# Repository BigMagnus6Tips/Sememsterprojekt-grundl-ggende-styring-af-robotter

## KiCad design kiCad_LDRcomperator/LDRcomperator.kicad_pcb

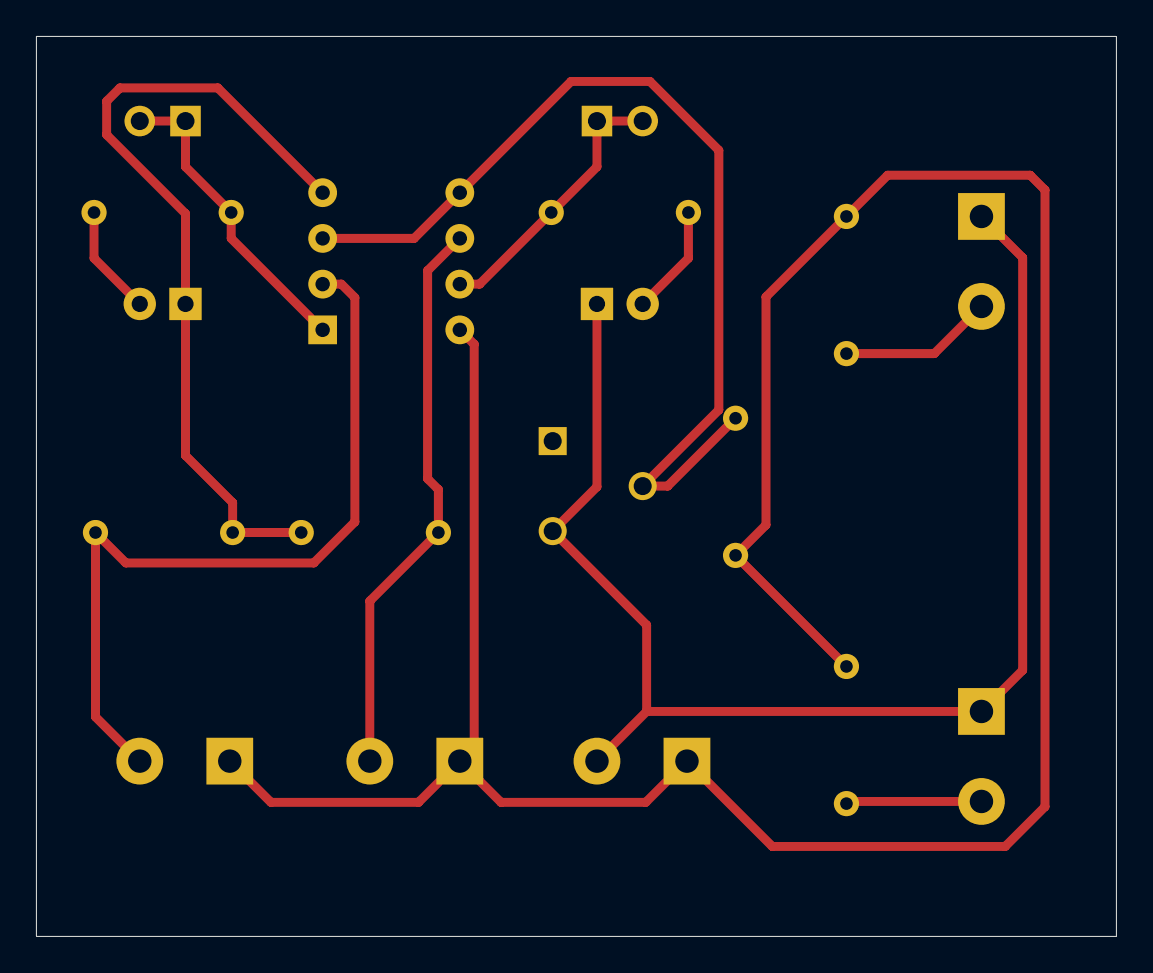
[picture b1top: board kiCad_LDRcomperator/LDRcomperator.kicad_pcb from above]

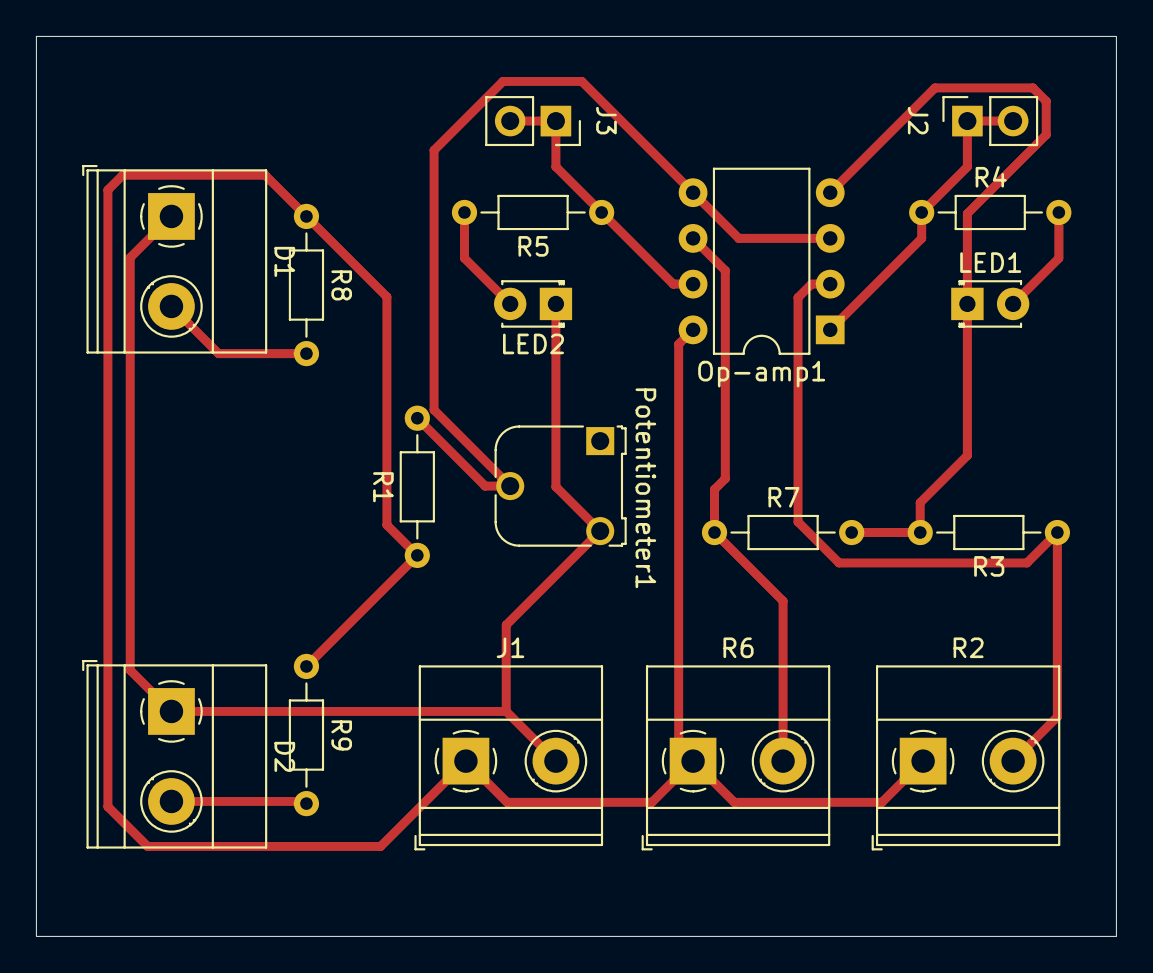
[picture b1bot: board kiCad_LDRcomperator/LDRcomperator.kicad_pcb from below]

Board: 2 copper layers, 60.0 x 50.0 mm, 18 parts (18 on the bottom side), 11 nets.

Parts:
D1, D2: LED; TerminalBlock_Phoenix_MKDS-1,5-2_1x02_P5.00mm_Horizontal
J1: Screw_Terminal_01x02; TerminalBlock_Phoenix_MKDS-1,5-2_1x02_P5.00mm_Horizontal
J2, J3: Conn_01x02_MountingPin; PinSocket_1x02_P2.54mm_Vertical
LED1, LED2: LED; LED_D1.8mm_W3.3mm_H2.4mm
Op-amp1: MCP6001R; DIP-8_W7.62mm
Potentiometer1: 100k ohm; Potentiometer_Runtron_RM-065_Vertical
R1: 22k ohm; R_Axial_DIN0204_L3.6mm_D1.6mm_P7.62mm_Horizontal
R2, R6: LDR03; TerminalBlock_Phoenix_MKDS-1,5-2_1x02_P5.00mm_Horizontal
R3: 2k ohm; R_Axial_DIN0204_L3.6mm_D1.6mm_P7.62mm_Horizontal
R4, R5: 65 ohm; R_Axial_DIN0204_L3.6mm_D1.6mm_P7.62mm_Horizontal
R7: 2,2k ohm; R_Axial_DIN0204_L3.6mm_D1.6mm_P7.62mm_Horizontal
R8, R9: 30; R_Axial_DIN0204_L3.6mm_D1.6mm_P7.62mm_Horizontal

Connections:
+3V3: J1.1, Op-amp1.8 (V+), R1.1, R2.1, R6.1, R8.1, R9.1
GND: D1.1 (K), D2.1 (K), J1.2, LED1.1 (K), LED2.1 (K), Op-amp1.4 (V-), Potentiometer1.3, R3.2, R7.2
unnamed: D1.2 (A), R8.2
unnamed: D2.2 (A), R9.2
unnamed: J2.1, J2.2, Op-amp1.1, R4.1
unnamed: J3.1, J3.2, Op-amp1.7, R5.1
unnamed: LED1.2 (A), R4.2
unnamed: LED2.2 (A), R5.2
unnamed: Op-amp1.3 (+), Op-amp1.5 (+), Potentiometer1.2, R1.2
unnamed: Op-amp1.2 (-), R2.2, R3.1
unnamed: Op-amp1.6 (-), R6.2, R7.1

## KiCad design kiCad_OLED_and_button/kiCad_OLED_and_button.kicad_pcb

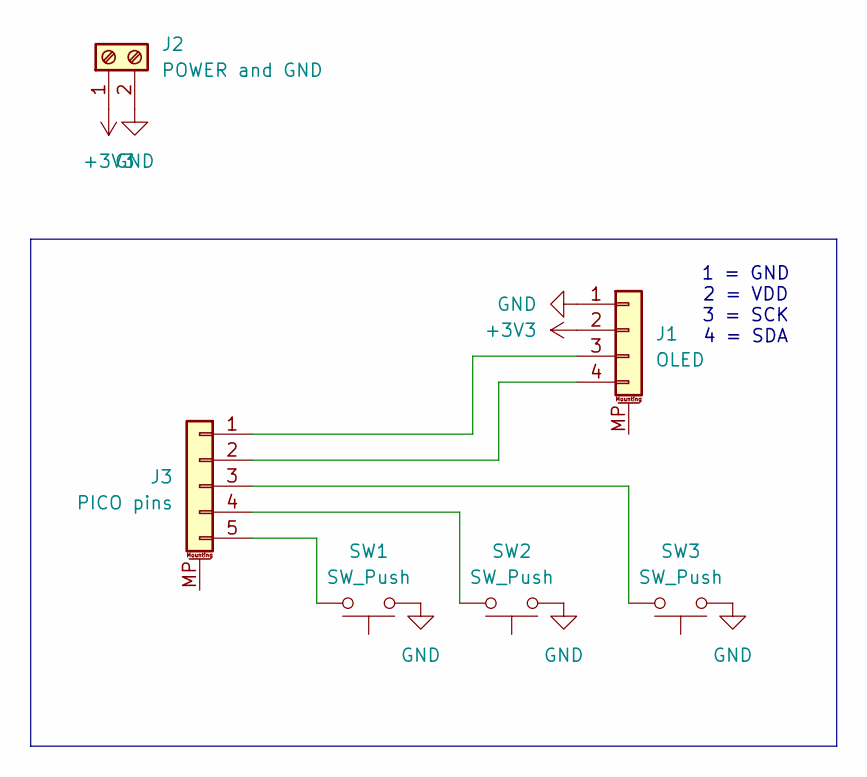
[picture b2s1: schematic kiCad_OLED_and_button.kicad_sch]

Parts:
J1: OLED; PinSocket_1x04_P2.54mm_Vertical
J2: POWER and GND; TerminalBlock_Phoenix_MKDS-1,5-2_1x02_P5.00mm_Horizontal
J3: PICO pins; PinSocket_1x05_P2.54mm_Vertical
SW1, SW2, SW3: SW_Push; SW_PUSH_6mm_H4.3mm

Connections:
+3V3: J1.2 (VDD), J2.1
GND: J1.1 (GND), J2.2, SW1.1, SW2.1, SW3.1
unnamed: J1.3 (SCK), J3.1
unnamed: J1.4 (SDA), J3.2
unnamed: J3.3, SW3.2
unnamed: J3.4, SW2.2
unnamed: J3.5, SW1.2

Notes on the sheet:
1 = GND 2 = VDD 3 = SCK 4 = SDA

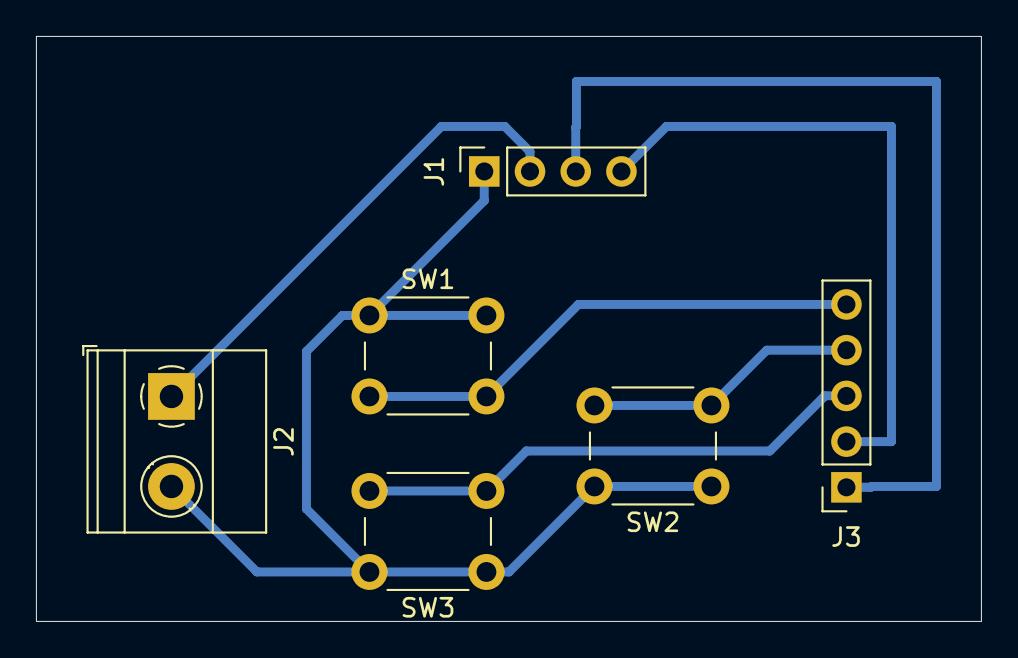
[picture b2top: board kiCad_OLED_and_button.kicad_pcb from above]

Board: 2 copper layers, 52.5 x 32.5 mm, 6 parts (0 on the bottom side), 7 nets.

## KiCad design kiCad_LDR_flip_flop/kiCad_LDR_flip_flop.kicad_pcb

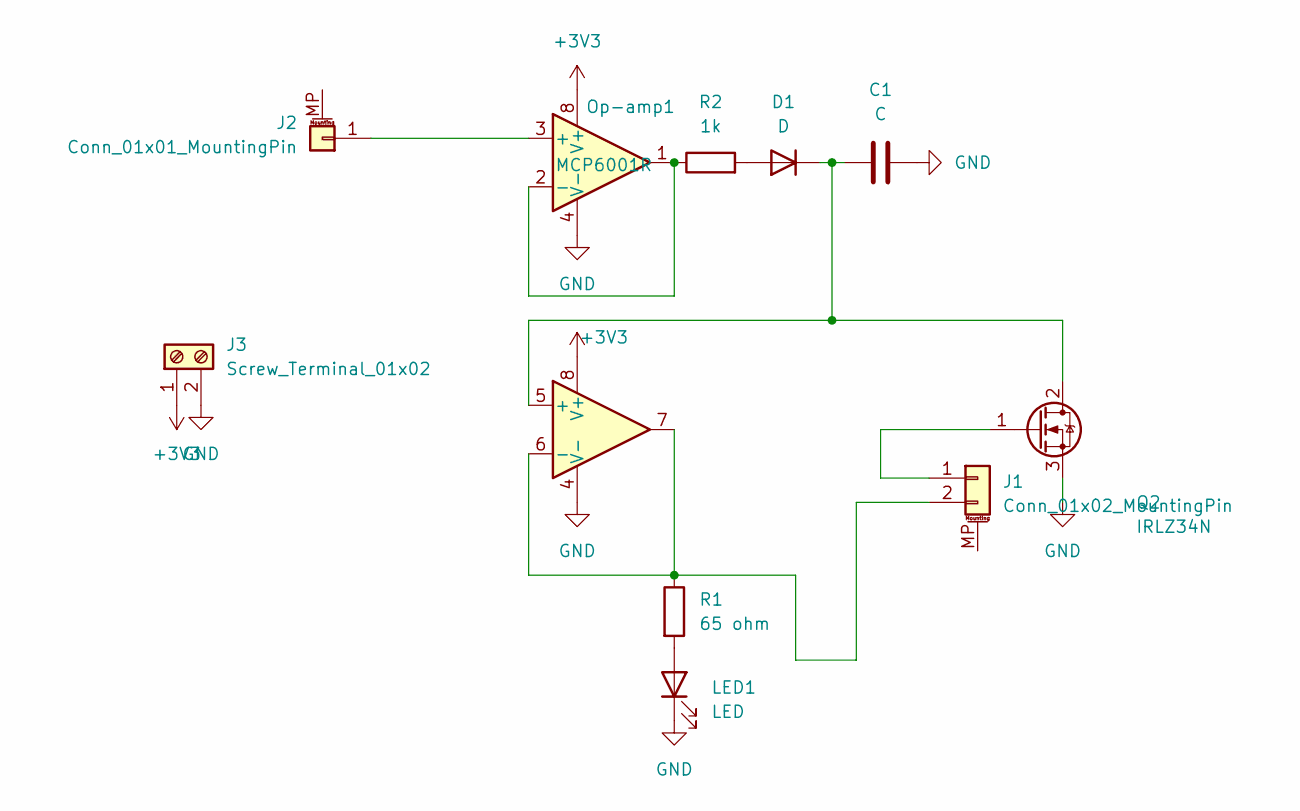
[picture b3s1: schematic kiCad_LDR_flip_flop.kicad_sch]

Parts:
C1: C; C_Disc_D11.0mm_W5.0mm_P5.00mm
D1: D; D_5W_P10.16mm_Horizontal
J1: Conn_01x02_MountingPin; PinSocket_1x02_P2.54mm_Vertical
J2: Conn_01x01_MountingPin; PinSocket_1x01_P2.54mm_Vertical
J3: Screw_Terminal_01x02; TerminalBlock_Phoenix_MKDS-1,5-2_1x02_P5.00mm_Horizontal
LED1: LED; LED_D1.8mm_W3.3mm_H2.4mm
Op-amp1: MCP6001R; DIP-8_W7.62mm
Q2: IRLZ34N; TO-220-3_Vertical
R1: 65 ohm; R_Axial_DIN0204_L3.6mm_D1.6mm_P7.62mm_Horizontal
R2: 1k; R_Axial_DIN0204_L3.6mm_D1.6mm_P7.62mm_Horizontal

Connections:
+3V3: J3.1, Op-amp1.8 (V+)
GND: C1.2, J3.2, LED1.1 (K), Op-amp1.4 (V-), Q2.3 (S)
unnamed: D1.2 (A), R2.2
unnamed: C1.1, D1.1 (K), Op-amp1.5 (+), Q2.2 (D)
unnamed: J1.1, Q2.1 (G)
unnamed: J1.2, Op-amp1.6 (-), Op-amp1.7, R1.1
unnamed: J2.1, Op-amp1.3 (+)
unnamed: LED1.2 (A), R1.2
unnamed: Op-amp1.1, Op-amp1.2 (-), R2.1

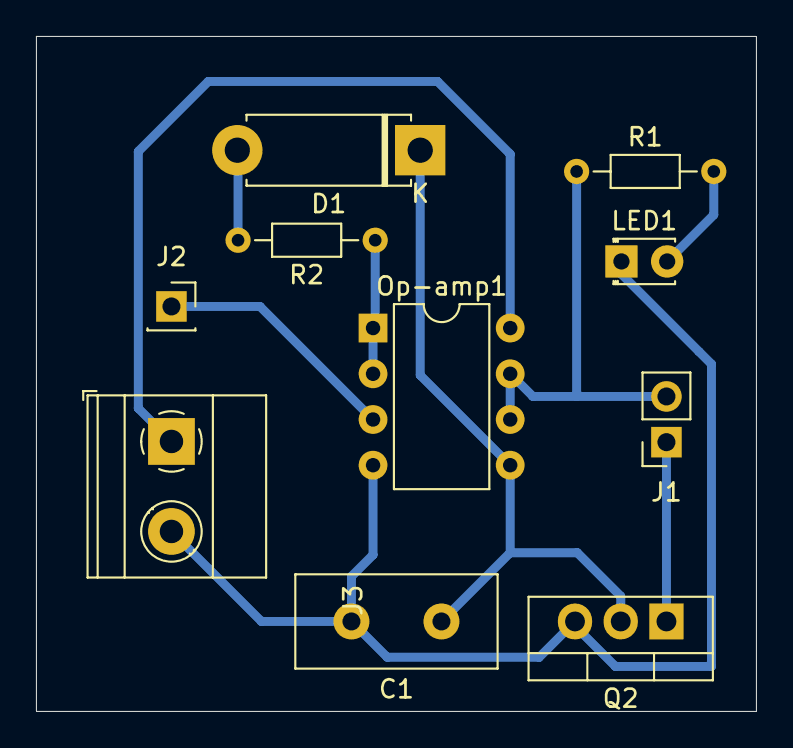
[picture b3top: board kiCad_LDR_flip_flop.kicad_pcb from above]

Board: 2 copper layers, 40.0 x 37.5 mm, 10 parts (0 on the bottom side), 9 nets.

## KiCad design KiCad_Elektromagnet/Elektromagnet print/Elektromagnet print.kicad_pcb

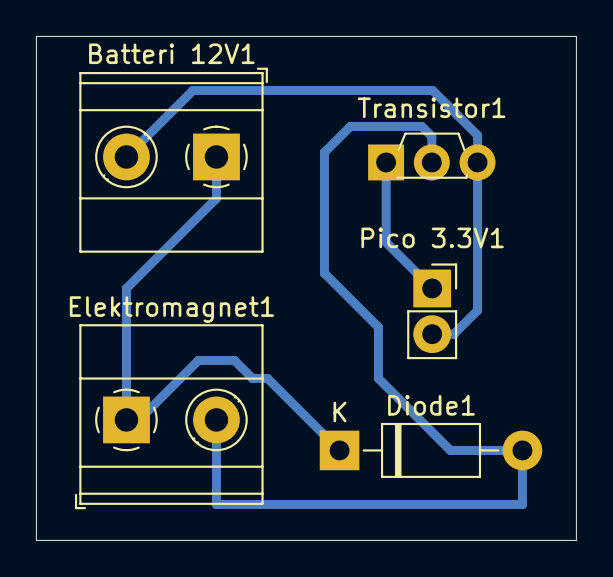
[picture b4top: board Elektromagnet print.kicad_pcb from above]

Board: 2 copper layers, 30.0 x 28.0 mm, 5 parts (0 on the bottom side), 4 nets.

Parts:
Batteri 12V1: Screw_Terminal_01x02; TerminalBlock_Phoenix_MKDS-1,5-2_1x02_P5.00mm_Horizontal
Diode1: 1N4001; D_DO-41_SOD81_P10.16mm_Horizontal
Elektromagnet1: L; TerminalBlock_Phoenix_MKDS-1,5-2_1x02_P5.00mm_Horizontal
Pico 3.3V1: Conn_01x01_Pin; PinSocket_1x02_P2.54mm_Vertical
Transistor1: 2N7000; TO-92S_Wide

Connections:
GND: Batteri 12V1.2, Pico 3.3V1.2 (Pin_1), Transistor1.3 (D)
unnamed: Batteri 12V1.1, Diode1.1 (K), Elektromagnet1.1
unnamed: Diode1.2 (A), Elektromagnet1.2, Transistor1.2 (G)
unnamed: Pico 3.3V1.1, Transistor1.1 (S)

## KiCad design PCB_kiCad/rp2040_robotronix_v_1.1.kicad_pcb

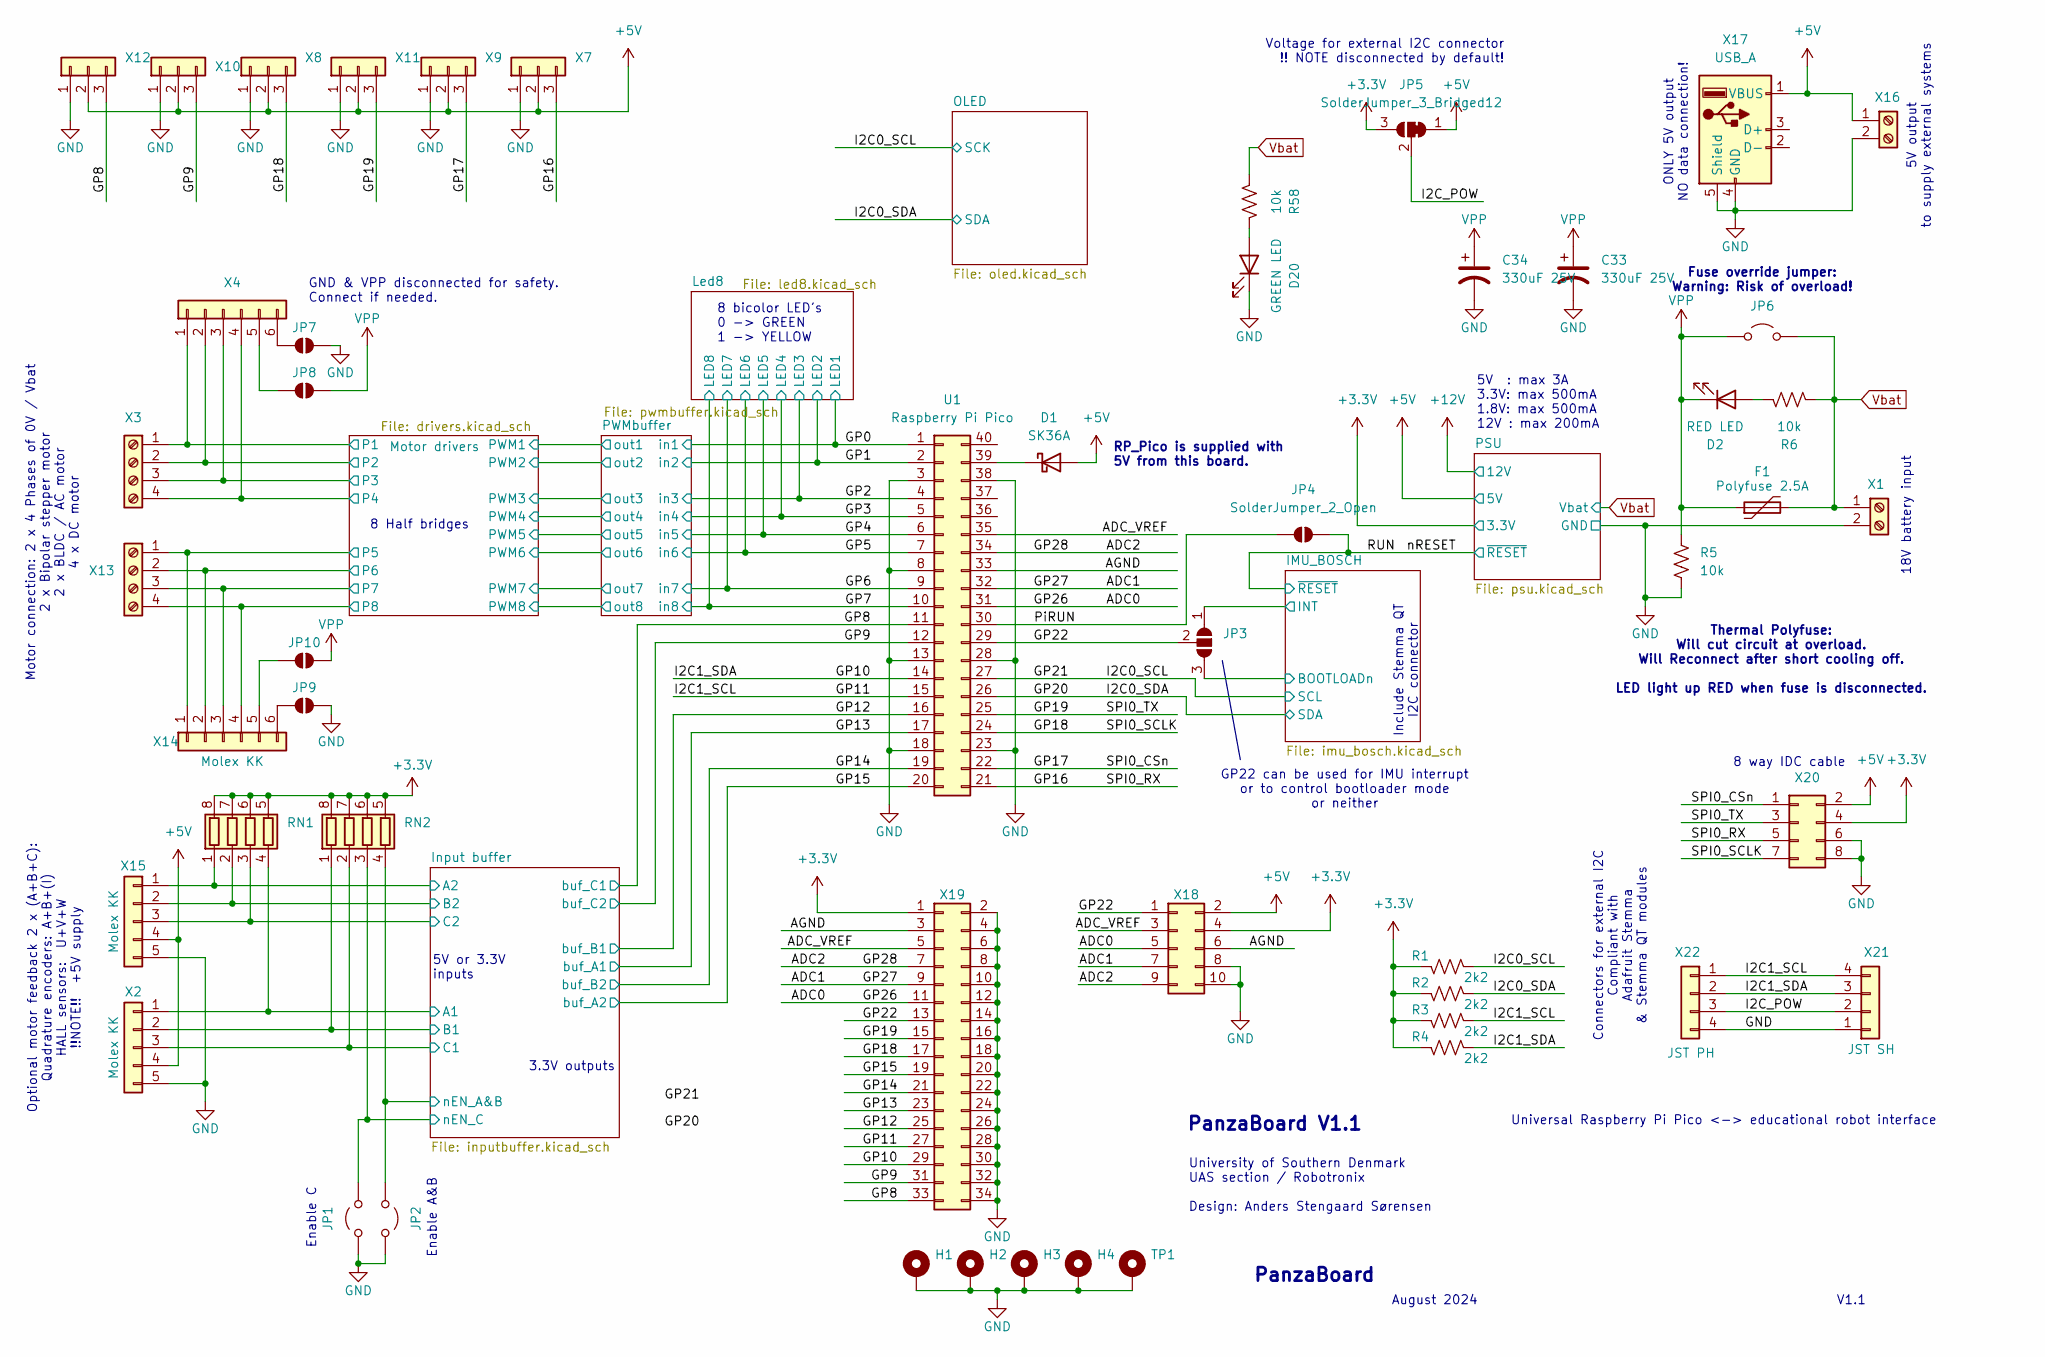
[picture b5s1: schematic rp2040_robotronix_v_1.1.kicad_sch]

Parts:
C33, C34: 330uF 25V; CP_Radial_D10.0mm_P5.00mm; MFR# Wurth Elektronik
D1: SK36A; D_SMA; MFR# Micro Commercial Components (MCC)
D2: RED LED; LED_0603_1608Metric; MFR# Wurth Elektronik
D20: GREEN LED; LED_0603_1608Metric; MFR# Wurth Elektronik
F1: Polyfuse 2.5A; Fuse_2920_7451Metric; MFR# Littlefuse
H1, H2, H3, H4: MountingHole_Pad; MountingHole_3.2mm_M3_Pad
JP1, JP2, JP6: Jumper_2_Open; SolderJumper-2_P1.3mm_Open_TrianglePad1.0x1.5mm
JP3: SolderJumper_3_Open; PinHeader_1x03_P2.54mm_Vertical
JP4, JP7, JP8, JP9, JP10: SolderJumper_2_Open; SolderJumper-2_P1.3mm_Open_Pad1.0x1.5mm
JP5: SolderJumper_3_Bridged12; SolderJumper-3_P1.3mm_Bridged12_Pad1.0x1.5mm_NumberLabels
R1, R2, R3, R4: 2k2; R_0603_1608Metric
R5, R6, R58: 10k; R_0603_1608Metric
RN1, RN2: 10k; R_Array_Convex_4x0402
TP1: MountingHole_Pad; MountingHole_3.2mm_M3_Pad
U1: Raspberry Pi Pico; RP_pico
X1: Screw_Terminal_01x02; TerminalBlock_Phoenix_PT-1,5-2-5.0-H_1x02_P5.00mm_Horizontal; MFR# Amphenol Anytek
X2, X15: Molex KK; Molex_KK-254_AE-6410-05A_1x05_P2.54mm_Vertical
X3, X13: Screw_Terminal_01x04; TerminalBlock_Phoenix_PT-1,5-4-3.5-H_1x04_P3.50mm_Horizontal; MFR# Phoenix Contact
X4: Conn_01x06; Molex_KK-254_AE-6410-06A_1x06_P2.54mm_Vertical
X7, X8, X9, X10, X11, X12: Conn_01x03; PinHeader_1x03_P2.54mm_Vertical
X14: Molex KK; Molex_KK-254_AE-6410-06A_1x06_P2.54mm_Vertical
X16: Screw_Terminal_01x02; TerminalBlock_Phoenix_PT-1,5-2-3.5-H_1x02_P3.50mm_Horizontal
X17: USB_A; USB_A_Molex_67643_Horizontal
X18: Conn_02x05_Odd_Even; IDC-Header_2x05_P2.54mm_Vertical
X19: Conn_02x17_Odd_Even; IDC-Header_2x17_P2.54mm_Vertical
X20: Conn_02x04_Odd_Even; PinHeader_2x04_P2.54mm_Vertical
X21: JST SH; JST_SH_SM04B-SRSS-TB_1x04-1MP_P1.00mm_Horizontal
X22: JST PH; JST_PH_S4B-PH-K_1x04_P2.00mm_Horizontal

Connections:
+5V: D1.2 (A), JP5.1 (A), X2.4, X7.2, X8.2, X9.2, X10.2, X11.2, X12.2, X15.4, X16.1, X17.1 (VBUS), X18.2, X20.2; also elsewhere on the board
/ADC0: U1.31, X18.5, X19.11
/ADC1: U1.32, X18.7, X19.9
/ADC2: U1.34, X18.9, X19.7
/ADC_VREF: U1.35, X18.3, X19.5
/AGND: U1.33, X18.6, X19.3
/GP0: U1.1; also elsewhere on the board
/GP1: U1.2; also elsewhere on the board
/GP2: U1.4; also elsewhere on the board
/GP3: U1.5; also elsewhere on the board
/GP4: U1.6; also elsewhere on the board
/GP5: U1.7; also elsewhere on the board
/GP6: U1.9; also elsewhere on the board
/GP7: U1.10; also elsewhere on the board
/GP8: U1.11, X12.3, X19.33; also elsewhere on the board
/GP9: U1.12, X10.3, X19.31; also elsewhere on the board
/GP10: R4.2, U1.14, X19.29, X21.3, X22.2
/GP11: R3.2, U1.15, X19.27, X21.4, X22.1
/GP12: U1.16, X19.25; also elsewhere on the board
/GP13: U1.17, X19.23; also elsewhere on the board
/GP14: U1.19, X19.21; also elsewhere on the board
/GP15: U1.20, X19.19; also elsewhere on the board
/GP16: U1.21, X7.3, X20.5
/GP17: U1.22, X9.3, X20.1
/GP18: U1.24, X8.3, X19.17, X20.7
/GP19: U1.25, X11.3, X19.15, X20.3
/GP20: R2.2, U1.26; also elsewhere on the board
/GP21: R1.2, U1.27; also elsewhere on the board
/GP22: JP3.2 (C), U1.29, X18.1, X19.13
/I2C_POW: JP5.2 (C), X21.2, X22.3
/IMU_BOSCH/BOOTLOADn: JP3.3 (B); also elsewhere on the board
/IMU_BOSCH/INT: JP3.1 (A); also elsewhere on the board
/Input buffer/A1: RN1.4 (R4.1), X2.1; also elsewhere on the board
/Input buffer/A2: RN1.1 (R1.1), X15.1; also elsewhere on the board
/Input buffer/B1: RN2.1 (R1.1), X2.2; also elsewhere on the board
/Input buffer/B2: RN1.2 (R2.1), X15.2; also elsewhere on the board
/Input buffer/C1: RN2.2 (R2.1), X2.3; also elsewhere on the board
/Input buffer/C2: RN1.3 (R3.1), X15.3; also elsewhere on the board
/Input buffer/nEN_A&B: JP2.2 (B), RN2.4 (R4.1); also elsewhere on the board
/Input buffer/nEN_C: JP1.2 (B), RN2.3 (R3.1); also elsewhere on the board
/Motor drivers/P1: X3.1, X4.1; also elsewhere on the board
/Motor drivers/P2: X3.2, X4.2; also elsewhere on the board
/Motor drivers/P3: X3.3, X4.3; also elsewhere on the board
/Motor drivers/P4: X3.4, X4.4; also elsewhere on the board
/Motor drivers/P5: X13.1, X14.1; also elsewhere on the board
/Motor drivers/P6: X13.2, X14.2; also elsewhere on the board
/Motor drivers/P7: X13.3, X14.3; also elsewhere on the board
/Motor drivers/P8: X13.4, X14.4; also elsewhere on the board
/PiRUN: JP4.1 (A), U1.30
/RUN: JP4.2 (B); also elsewhere on the board
GND: C33.2, C34.2, D20.1 (K), H1.1, H2.1, H3.1, H4.1, JP1.1 (A), JP2.1 (A), JP7.2 (B), JP9.2 (B), R5.1, TP1.1, U1.3, U1.8, U1.13, U1.18, U1.23, U1.28, U1.38, X1.2, X2.5, X7.1, X8.1, X9.1, X10.1, X11.1, X12.1, X15.5, X16.2, X17.4 (GND), X17.5 (Shield), X18.8, X18.10, X19.2, X19.4, X19.6, X19.8, X19.10, X19.12, X19.14, X19.16, X19.18, X19.20, X19.22, X19.24, X19.26, X19.28, X19.30, X19.32, X19.34, X20.6, X20.8, X21.1, X22.4; also elsewhere on the board
unnamed: D1.1 (K), U1.39
unnamed: D2.2 (A), R6.1
unnamed: D20.2 (A), R58.1
unnamed: JP7.1 (A), X4.6
unnamed: JP8.1 (A), X4.5
unnamed: JP9.1 (A), X14.6
unnamed: JP10.1 (A), X14.5
SD: JP5.3 (B), R1.1, R2.1, R3.1, R4.1, RN1.5 (R4.2), RN1.6 (R3.2), RN1.7 (R2.2), RN1.8 (R1.2), RN2.5 (R4.2), RN2.6 (R3.2), RN2.7 (R2.2), RN2.8 (R1.2), X18.4, X19.1, X20.4; also elsewhere on the board
VPP: C33.1, C34.1, D2.1 (K), F1.1, JP6.1 (A), JP8.2 (B), JP10.2 (B), R5.2; also elsewhere on the board
Vbat: F1.2, JP6.2 (B), R6.2, R58.2, X1.1; also elsewhere on the board

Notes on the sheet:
8 bicolor LED's 0 -> GREEN 1 -> YELLOW
Motor connection: 2 x 4 Phases of 0V / Vbat 2 x Bipolar stepper motor 2 x BLDC / AC motor 4 x DC motor
PanzaBoard V1.1
8 Half bridges
Connectors for external I2C Compliant with Adafruit Stemma & Stemma QT modules
Fuse override jumper: Warning: Risk of overload!
Enable A&B
Universal Raspberry Pi Pico <-> educational robot interface
PanzaBoard
RP_Pico is supplied with 5V from this board.
5V output to supply external systems
5V : max 3A 3.3V: max 500mA 1.8V: max 500mA 12V : max 200mA
V1.1
5V or 3.3V inputs
ONLY 5V output NO data connection!
8 way IDC cable
Optional motor feedback 2 x (A+B+C): Quadrature encoders: A+B+(I) HALL sensors: U+V+W !!NOTE!! +5V supply
August 2024
GP22 can be used for IMU interrupt or to control bootloader mode or neither
University of Southern Denmark UAS section / Robotronix Design: Anders Stengaard Sørensen
18V battery input
3.3V outputs
Enable C
Thermal Polyfuse: Will cut circuit at overload. Will Reconnect after short cooling off. LED light up RED when fuse is disconnected.
GND & VPP disconnected for safety. Connect if needed.
Include Stemma QT I2C connector
Voltage for external I2C connector !! NOTE disconnected by default!

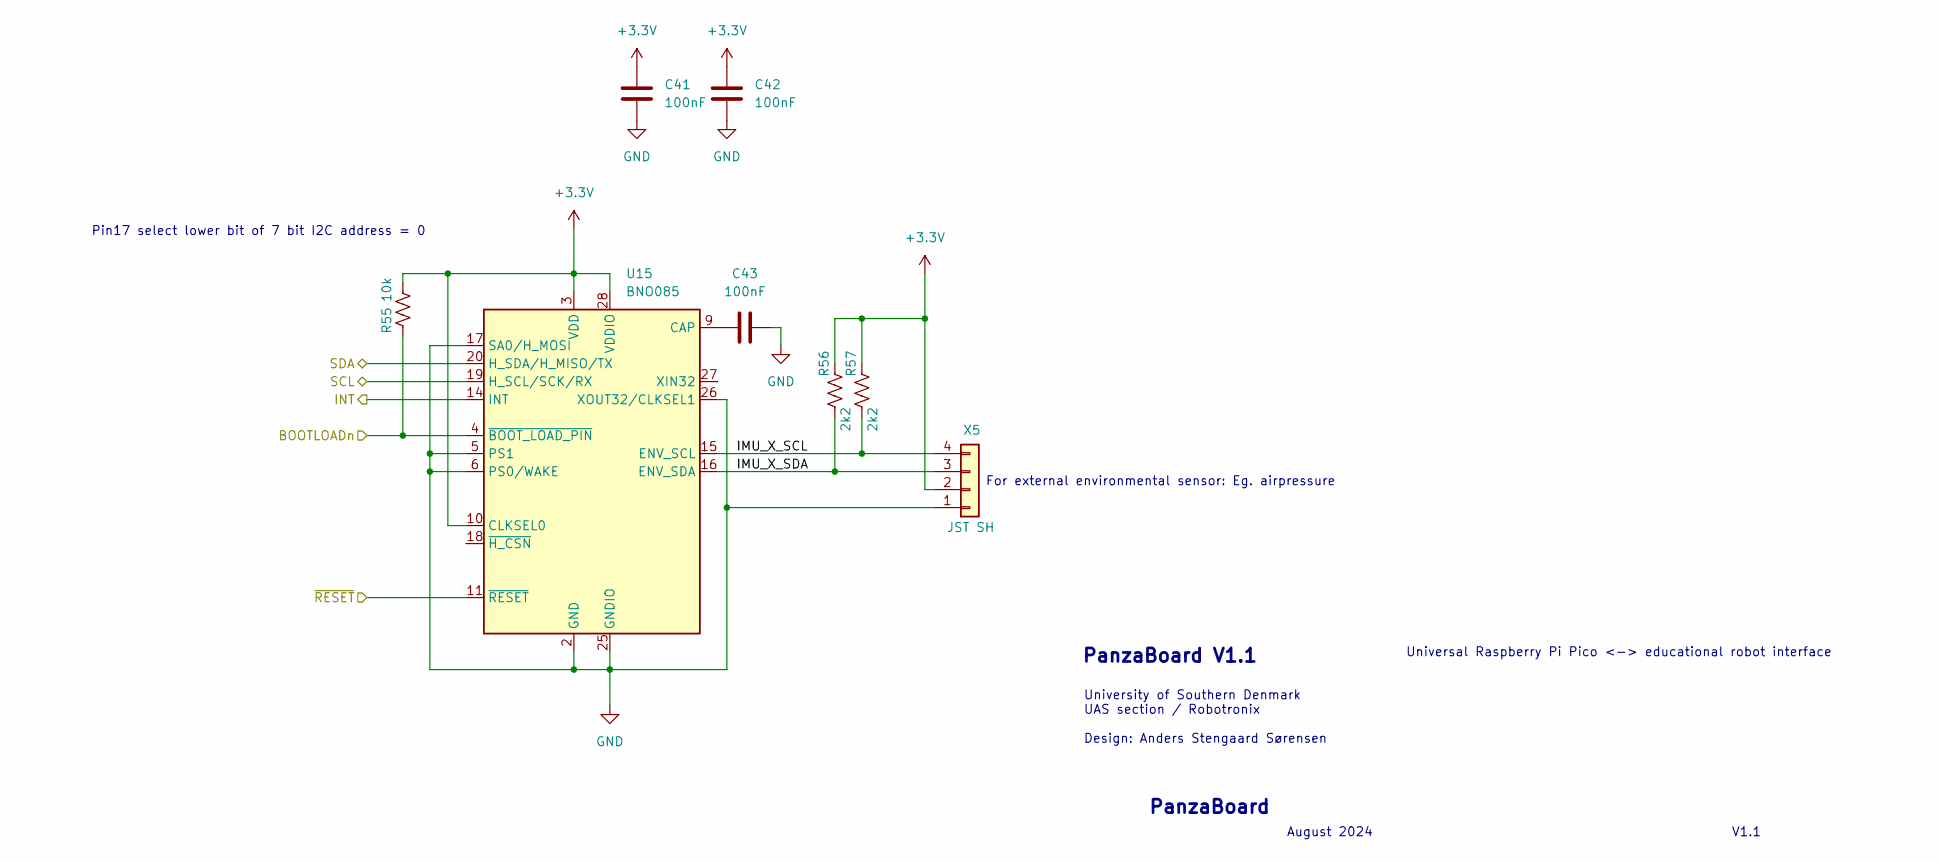
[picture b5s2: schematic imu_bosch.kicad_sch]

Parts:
C41, C42, C43: 100nF; C_0603_1608Metric
R55: 10k; R_0603_1608Metric
R56, R57: 2k2; R_0603_1608Metric
U15: BNO085; LGA-28_5.2x3.8mm_P0.5mm; MFR# CEVA
X5: JST SH; JST_SH_SM04B-SRSS-TB_1x04-1MP_P1.00mm_Horizontal

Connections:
/GP20: U15.20 (H_SDA/H_MISO/TX); also elsewhere on the board
/GP21: U15.19 (H_SCL/SCK/RX); also elsewhere on the board
/IMU_BOSCH/BOOTLOADn: R55.1, U15.4 (~BOOT_LOAD_PIN); also elsewhere on the board
/IMU_BOSCH/IMU_X_SCL: R57.2, U15.15 (ENV_SCL), X5.4
/IMU_BOSCH/IMU_X_SDA: R56.2, U15.16 (ENV_SDA), X5.3
/IMU_BOSCH/INT: U15.14 (INT); also elsewhere on the board
/RUN: U15.11 (~RESET); also elsewhere on the board
GND: C41.1, C42.1, C43.2, U15.2 (GND), U15.5 (PS1), U15.6 (PS0/WAKE), U15.17 (SA0/H_MOSI), U15.25 (GNDIO), U15.26 (XOUT32/CLKSEL1), X5.1; also elsewhere on the board
unnamed: C43.1, U15.9 (CAP)
SD: C41.2, C42.2, R55.2, R56.1, R57.1, U15.3 (VDD), U15.10 (CLKSEL0), U15.28 (VDDIO), X5.2; also elsewhere on the board

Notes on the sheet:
University of Southern Denmark UAS section / Robotronix Design: Anders Stengaard Sørensen
PanzaBoard V1.1
August 2024
Universal Raspberry Pi Pico <-> educational robot interface
For external environmental sensor: Eg. airpressure
PanzaBoard
V1.1
Pin17 select lower bit of 7 bit I2C address = 0

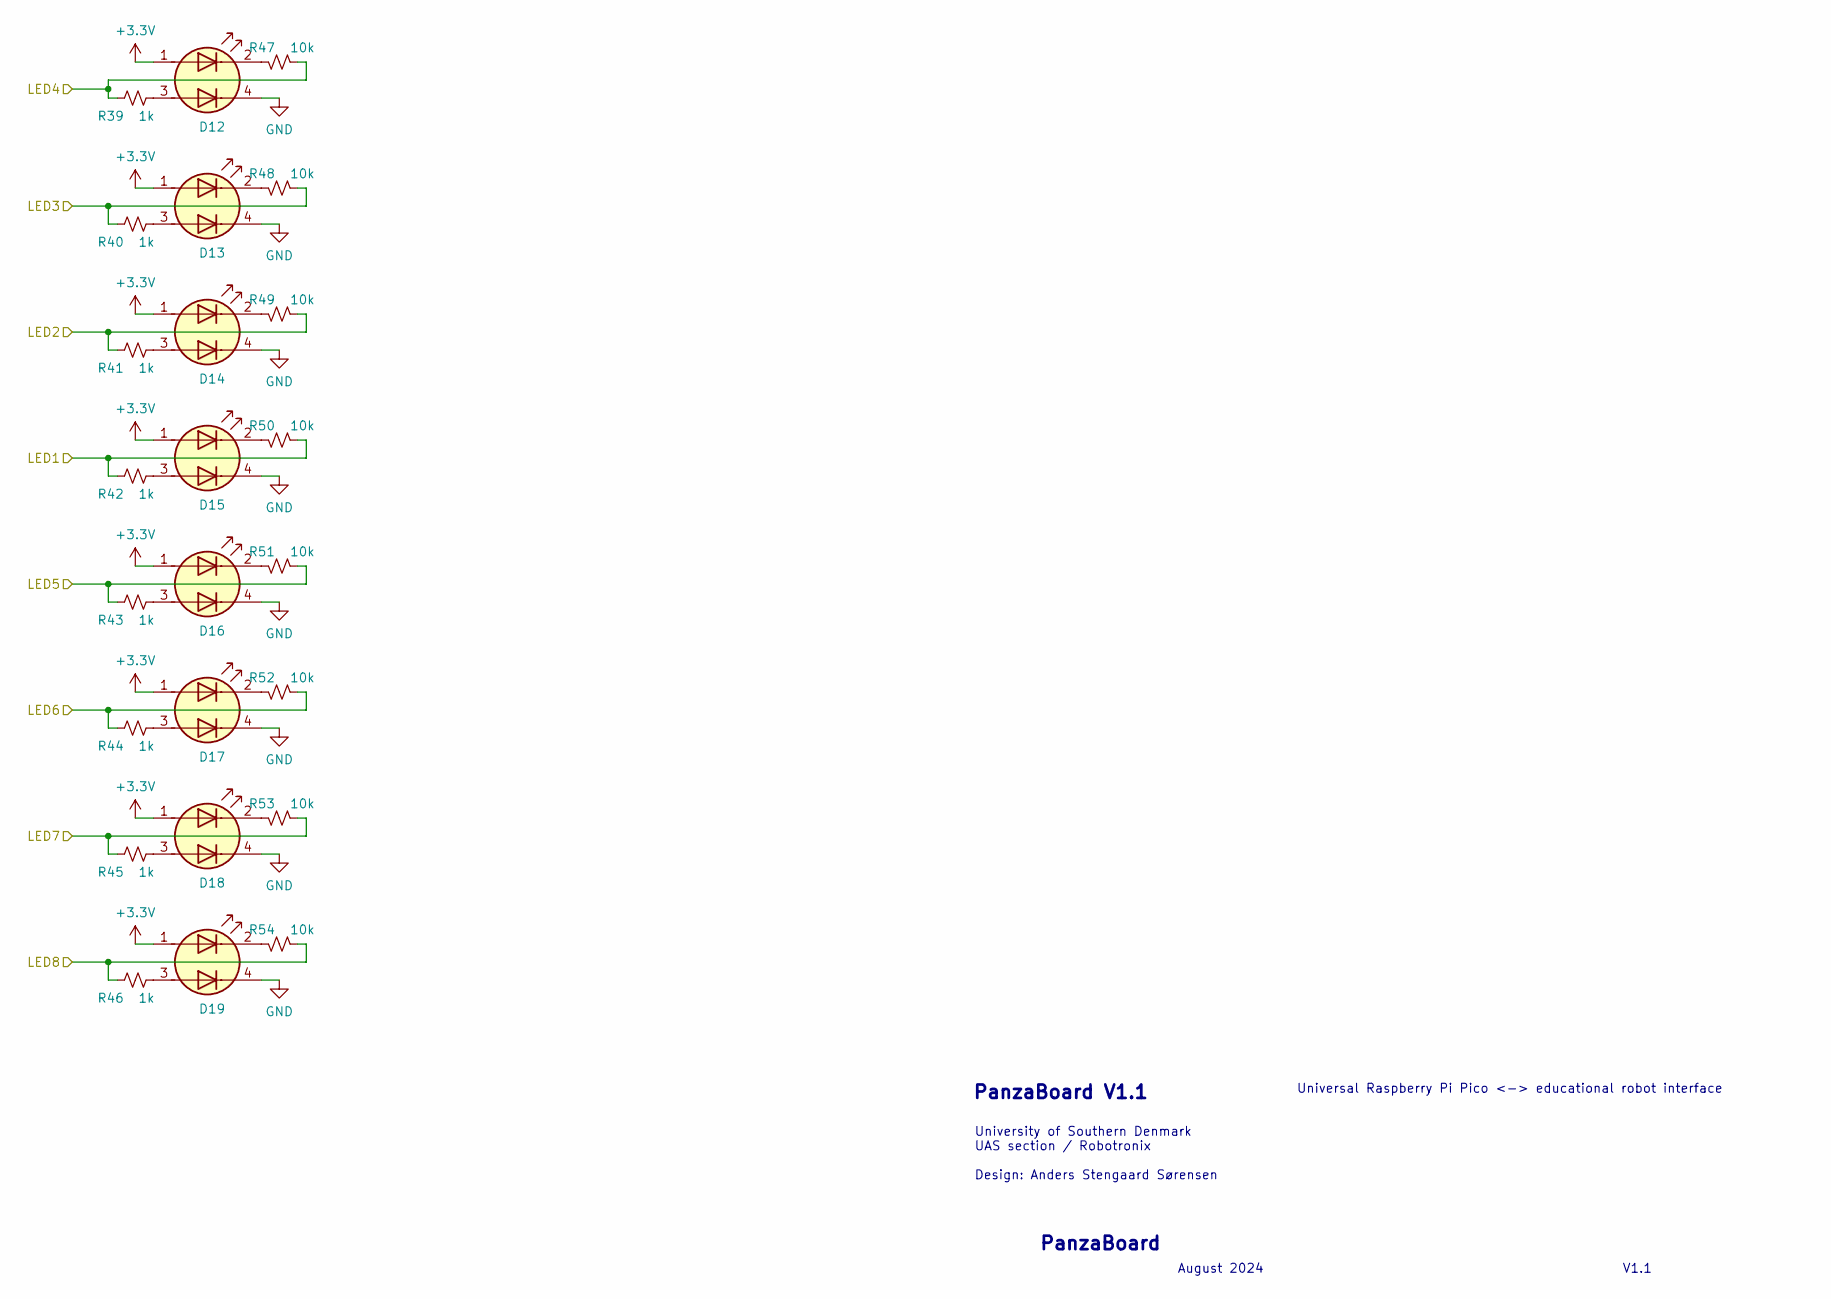
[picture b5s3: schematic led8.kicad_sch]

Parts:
D12, D13, D14, D15, D16, D17, D18, D19: LED_Dual_AKAK; LED_DUAL_3.2x2.7_Kingbright
R39, R40, R41, R42, R43, R44, R45, R46: 1k; R_0603_1608Metric
R47, R48, R49, R50, R51, R52, R53, R54: 10k; R_0603_1608Metric

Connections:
/GP0: R42.1, R50.2; also elsewhere on the board
/GP1: R41.1, R49.2; also elsewhere on the board
/GP2: R40.1, R48.2; also elsewhere on the board
/GP3: R39.1, R47.2; also elsewhere on the board
/GP4: R43.1, R51.2; also elsewhere on the board
/GP5: R44.1, R52.2; also elsewhere on the board
/GP6: R45.1, R53.2; also elsewhere on the board
/GP7: R46.1, R54.2; also elsewhere on the board
GND: D12.4 (K2), D13.4 (K2), D14.4 (K2), D15.4 (K2), D16.4 (K2), D17.4 (K2), D18.4 (K2), D19.4 (K2); also elsewhere on the board
unnamed: D12.3 (A2), R39.2
unnamed: D12.2 (K1), R47.1
unnamed: D13.3 (A2), R40.2
unnamed: D13.2 (K1), R48.1
unnamed: D14.3 (A2), R41.2
unnamed: D14.2 (K1), R49.1
unnamed: D15.3 (A2), R42.2
unnamed: D15.2 (K1), R50.1
unnamed: D16.3 (A2), R43.2
unnamed: D16.2 (K1), R51.1
unnamed: D17.3 (A2), R44.2
unnamed: D17.2 (K1), R52.1
unnamed: D18.3 (A2), R45.2
unnamed: D18.2 (K1), R53.1
unnamed: D19.3 (A2), R46.2
unnamed: D19.2 (K1), R54.1
SD: D12.1 (A1), D13.1 (A1), D14.1 (A1), D15.1 (A1), D16.1 (A1), D17.1 (A1), D18.1 (A1), D19.1 (A1); also elsewhere on the board

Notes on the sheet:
University of Southern Denmark UAS section / Robotronix Design: Anders Stengaard Sørensen
Universal Raspberry Pi Pico <-> educational robot interface
August 2024
V1.1
PanzaBoard
PanzaBoard V1.1
